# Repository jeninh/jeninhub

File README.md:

# jeninhub
A USB hub with 2 USB-A and 2 USB-C slots. Plugs into your laptop's USB-C slot.  

Made by @jeninh   

Contains:
- USB-C input
- 2 USB-C Ports
- 2 USB-A Ports
- Crystal + SL2.1A for MAXIMUM EFFICIENCY
- Mounted via mounting holes (2.2mm)
- 3d Printed Case

# Information :D
I made this because I just got a new laptop (yaaaay!!) and I wanted more ports. I also have a setup that connects my laptop to a wireless mouse, mic, monitor, etc when it's on my desk and I wanted to plug them all in at once!  
This hub has 2 USB-C ports and 1 USB-A ports

# PCB!!! THIS TOOK ME SO LONG 😭

This is the schematic! See that i also added a crystal connected to the SL2.1A :D so yeah

Front:

Back:

3d Preview after assembly:

Done in Kicad (the goat)... so yeah

# Case
DONE IN FUSION 360... OH MY DAYS THIS TOOK SO LONG

Difficulties I had with the case:
- LINING UP THE HOLES.... UGH MY MEASUREMENT SKILLS ARE DISGUSTING
- Sizing the height... I had to adjust this multiple times, especially after adding and switching the crystal
- Using fusion360 😭this is like my 2nd time

## BOM

| Name                 | Qty | Price (USD) | Link                          |
|----------------------|-----|-------------|-------------------------------|
| PCBA                 | 2   | NA          | Out of Pocket                 |
| PCB                  | 5   | NA          | Out of Pocket                 |
| USB-C to USB-C cable | 1   | NA          | Out of Pocket                 |
| M2 x 6mm Screws      | 4   | NA          | Self Sourced                  |
| M2 Nuts              | 4   | NA          | Self Sourced                  |
| Top Case             | 1   | NA          | Self Printed                  |
| Bottom Case          | 1   | NA          | Self Printed                  |
*after taxes and conversion from CAD to USD. this is the cheapest USB-C product I can find that can come in time
    
Now... you may be wondering... why am I getting all these out of pocket?    
Well... I need to finish my project by August 7 which is about 9 days from when I am writing this and I defenitely won't get expedited shipping for free... so I might as well pay for my PCB and PCBA out of pocket so I get it on time!    
For the rest of the items... I am 3d printing the case myself and I have screws and nuts :)

## Notes
I like trains     
Rudy and Valen are goated for helping me with this      
Please accept me 😭 I am literally doing all of this out of pocket except for US$5 😭

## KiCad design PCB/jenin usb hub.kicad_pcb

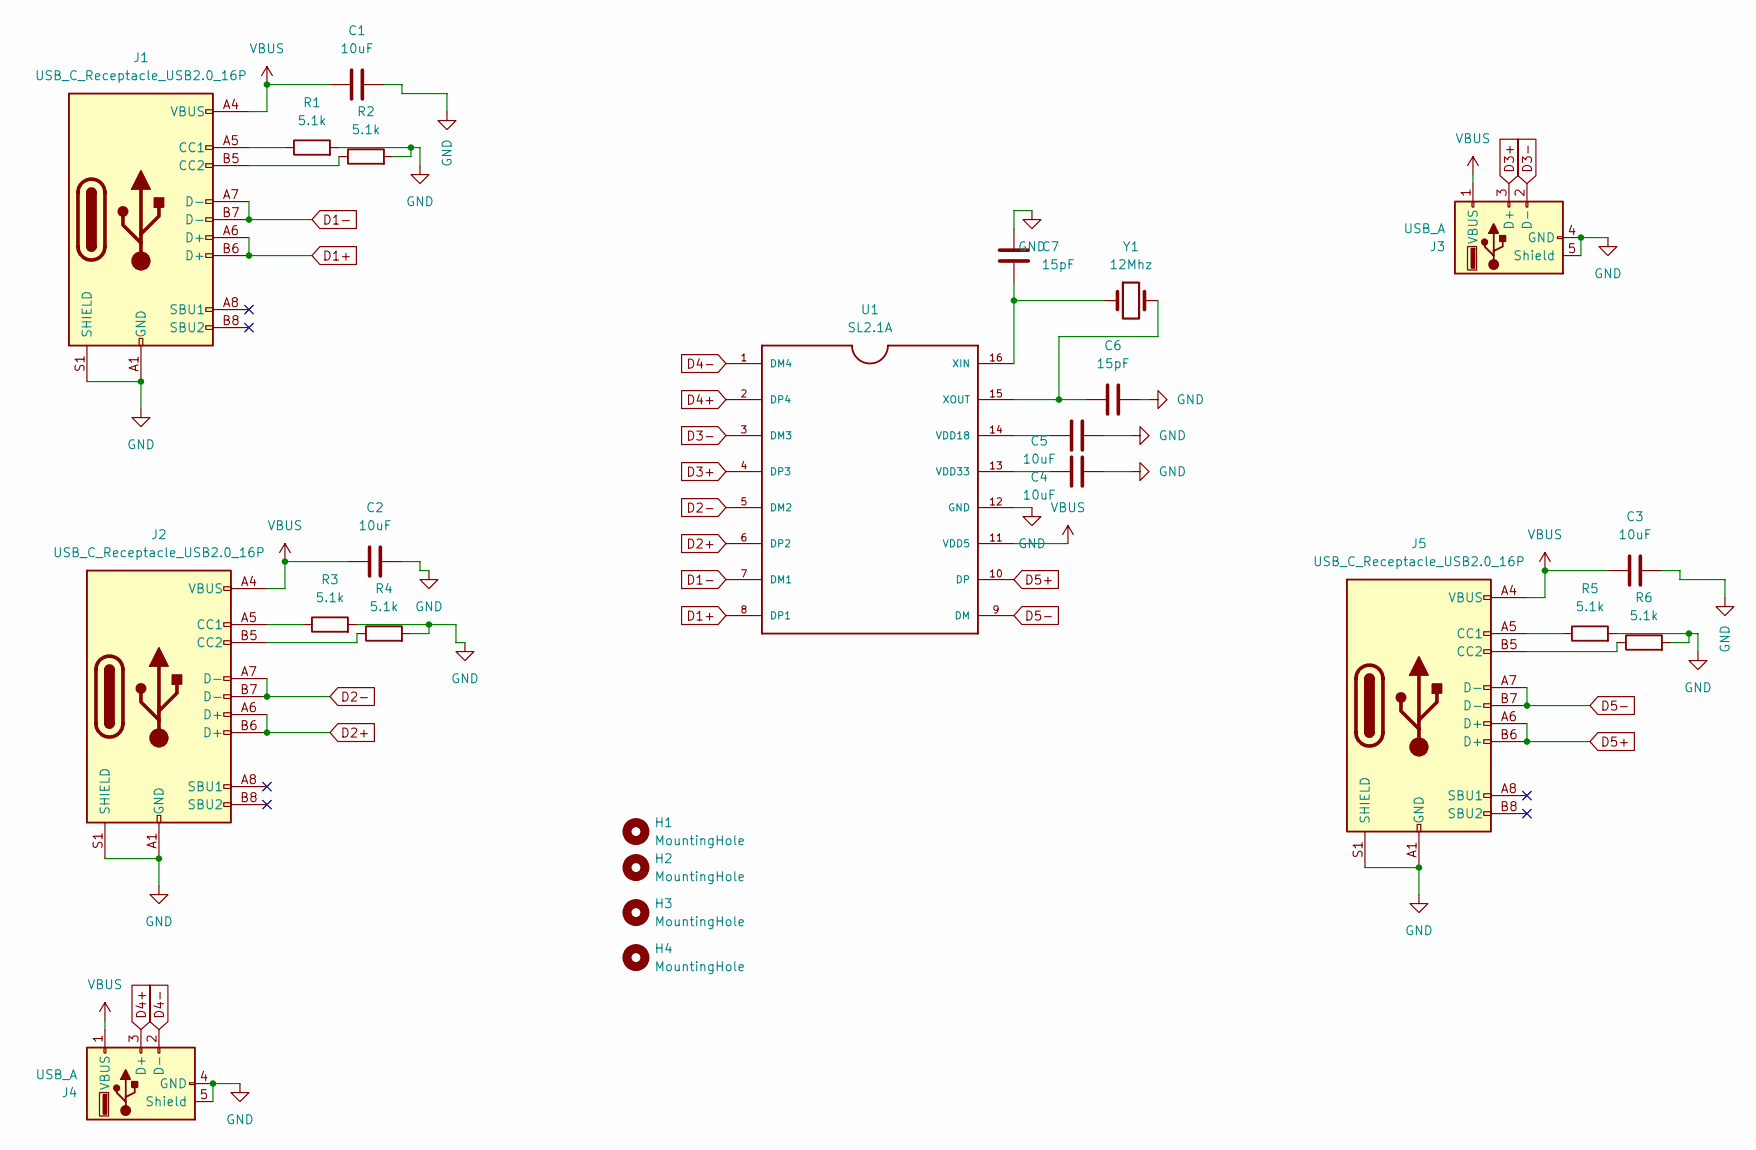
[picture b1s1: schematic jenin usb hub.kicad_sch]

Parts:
C1, C2, C3, C4, C5: 10uF; C_0805_2012Metric
C6, C7: 15pF; C_0805_2012Metric
H1, H2, H3, H4: MountingHole; MountingHole_2.2mm_M2
J1, J2, J5: USB_C_Receptacle_USB2.0_16P; USB_C_Receptacle_G-Switch_GT-USB-7010ASV
J3, J4: USB_A; USB_A_Receptacle_GCT_USB1046
R1, R2, R3, R4, R5, R6: 5.1k; R_0603_1608Metric
U1: SL2.1A; SO16
Y1: 12Mhz; Crystal_SMD_3225-4Pin_3.2x2.5mm

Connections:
D1+: J1.A6 (D+), J1.B6 (D+), U1.8 (DP1)
D1-: J1.A7 (D-), J1.B7 (D-), U1.7 (DM1)
D2+: J2.A6 (D+), J2.B6 (D+), U1.6 (DP2)
D2-: J2.A7 (D-), J2.B7 (D-), U1.5 (DM2)
D3+: J3.3 (D+), U1.4 (DP3)
D3-: J3.2 (D-), U1.3 (DM3)
D4+: J4.3 (D+), U1.2 (DP4)
D4-: J4.2 (D-), U1.1 (DM4)
D5+: J5.A6 (D+), J5.B6 (D+), U1.10 (DP)
D5-: J5.A7 (D-), J5.B7 (D-), U1.9 (DM)
GND: C1.2, C2.2, C3.2, C4.2, C5.2, C6.1, C7.1, J1.A1 (GND), J1.A12 (GND), J1.B1 (GND), J1.B12 (GND), J1.S1 (SHIELD), J2.A1 (GND), J2.A12 (GND), J2.B1 (GND), J2.B12 (GND), J2.S1 (SHIELD), J3.4 (GND), J3.5 (Shield), J4.4 (GND), J4.5 (Shield), J5.A1 (GND), J5.A12 (GND), J5.B1 (GND), J5.B12 (GND), J5.S1 (SHIELD), R1.2, R2.2, R3.2, R4.2, R5.2, R6.2, U1.12 (GND)
unnamed: J1.A5 (CC1), R1.1
unnamed: J1.B5 (CC2), R2.1
unnamed: J2.A5 (CC1), R3.1
unnamed: J2.B5 (CC2), R4.1
unnamed: J5.A5 (CC1), R5.1
unnamed: J5.B5 (CC2), R6.1
unnamed: C5.1, U1.14 (VDD18)
unnamed: C4.1, U1.13 (VDD33)
unnamed: C7.2, U1.16 (XIN), Y1.1
unnamed: C6.2, U1.15 (XOUT), Y1.2
VBUS: C1.1, C2.1, C3.1, J1.A4 (VBUS), J1.A9 (VBUS), J1.B4 (VBUS), J1.B9 (VBUS), J2.A4 (VBUS), J2.A9 (VBUS), J2.B4 (VBUS), J2.B9 (VBUS), J3.1 (VBUS), J4.1 (VBUS), J5.A4 (VBUS), J5.A9 (VBUS), J5.B4 (VBUS), J5.B9 (VBUS), U1.11 (VDD5)

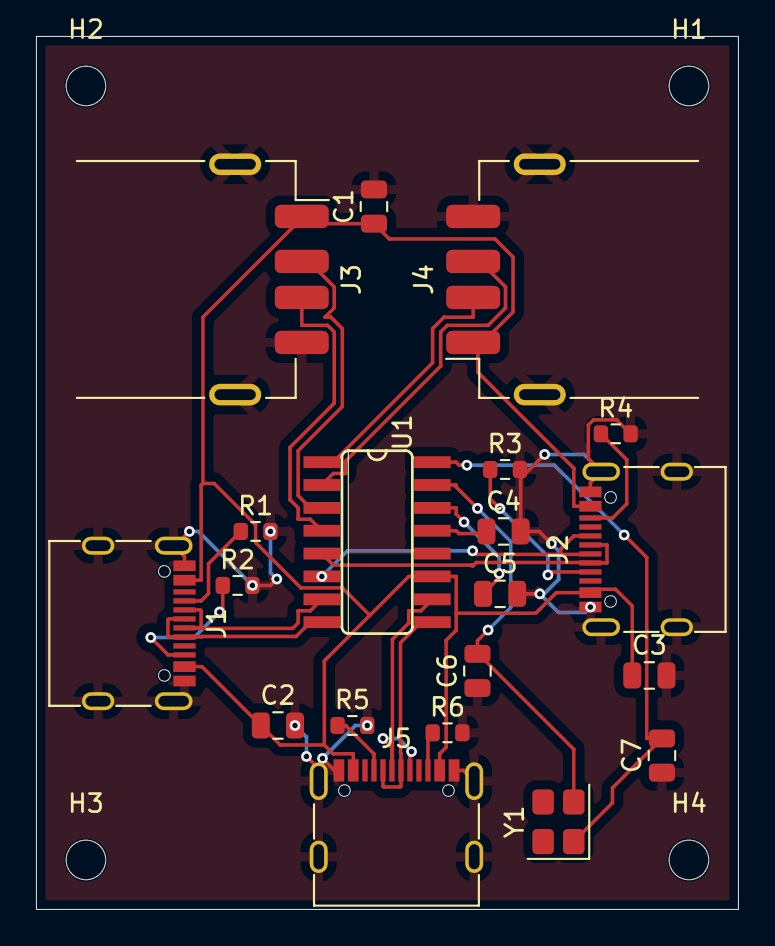
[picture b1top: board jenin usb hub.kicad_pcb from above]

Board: 2 copper layers, 39.0 x 48.5 mm, 24 parts (0 on the bottom side), 22 nets.

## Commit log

2025-09-15 Add assembly section and PCB issue notes
    Documented assembly work and PCB issues encountered.
